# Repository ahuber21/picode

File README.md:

# picode - All code that is run on the Saufhaengerle Raspberry Pi

* [picode - All code that is run on the Saufhaengerle Raspberry Pi](#picode---all-code-that-is-run-on-the-saufhaengerle-raspberry-pi)
  * [Links](#links)
  * [TODO](#todo)
  * [Contents](#contents)
    * [switcher](#switcher)
    * [zapfhahn](#zapfhahn)
  * [Timezone notes](#timezone-notes)
  * [Install pyfingerprint](#install-pyfingerprint)
    * [pyfingerprint - required modifications / hacks](#pyfingerprint---required-modifications--hacks)
  * [Fixing the image download from charBuffer](#fixing-the-image-download-from-charbuffer)
    * [Using fingerprint sensor](#using-fingerprint-sensor)
  * [Valve notes](#valve-notes)
  * [MariaDB notes](#mariadb-notes)
    * [phpMyAdmin](#phpmyadmin)
    * [Grafana](#grafana)

## Links

* saufanlage myPhpAdmin: http://saufanlage.local:81/http://saufanlage.local:81/phpmyadmin/
  * suffi - NU-AD-76
* saufanlage grafana: http://saufanlage.local:3000
  * admin - NU-AD-76

## TODO

* Multiple fingers per user
  * Fingerprint class?
* Only valves that are registered for user
* Auto-close when idle, i.e. no quantity for x seconds
* Logs to website
* Web terminal
* Android app with push notifications
  * some statistics for every tap
* Web interface for valve/daemon configuration
* Web interface to start calib?
* Warning when tapped quantity threshold is reached
* 4 digit display

Code here is set up for python version 3.X and all required packages are defined in `requirements.txt`.

To set up the RPi do

```bash
# first make sure you installed python3.X + some dev libs
sudo apt-get install python3 python3-dev libtiff5-dev zlib1g-dev libfreetype6-dev liblcms2-dev libwebp-dev libharfbuzz-dev libfribidi-dev tcl8.6-dev tk8.6-dev python-tk git python3-venv emacs devscripts equivs libjpeg-dev apt-get install python3-dev
```

(most of the requirements are for `Pillow` which is required by pyfingerprint)

Now set up the virtual environment

```bash
git clone --recursive https://gitlab.com/saufhaengerle/picode
cd picode
python3.7 -m venv venv
source venv/bin/activate
pip install -r requirements.txt
```

If you want to set up the repository for development, **additional steps** are required. After completing the steps above do

```bash
pre-commit install
```

## Contents

### switcher

A webapp that can switch attached relays. Usually used for switching lights.

Notes:

* Bootstrap version 2.3.2
* Bootstrap toggle from http://www.bootstraptoggle.com/

### zapfhahn

All the code that is required to run the Zapfhahn.

## Timezone notes

Make sure that you select the correct timezone!

```bash
$ sudo raspi-config
# select Europe/Berlin in option '4. Localisation options'
```

## Install pyfingerprint

```bash
# dirty hack because pip install does not actually install the package, only sets the context
mkdir venv/lib/python3.5/site-packages/pyfingerprint
cp src/zapfhahn/hardware/pyfingerprint/src/files/pyfingerprint/pyfingerprint.py venv/lib/python3.5/site-packages/pyfingerprint
```

In order to use the Raspberry Pi's serial port I had to make change that is explained [here](https://raspberrypi.stackexchange.com/questions/45570/how-do-i-make-serial-work-on-the-raspberry-pi3-pi3b-pizerow/45571#45571). More informatio$

Do

```bash
sudo emacs -nw /boot/config.txt
```

and add the lines

```
enable_uart=1
dtoverlay=pi3-disable-bt
```

Further /boot/cmdline.txt needs some editing to prevent the console from using the UART

```bash
sudo emacs -nw /boot/cmdline.txt
```

and remove the following entry

```
console=serial0,115200
```

It is also necessary to disable the system service that initialises the modem so it doesn't use the UART: `sudo systemctl disable hciuart`.

After rebooting, this will make the uart pins available as `/dev/ttyAMA0` or better `/dev/serial0`.

To install minicom use

```bash
$ sudo apt-get install minicom
```

Now you can test the serial port, shortcut TX and RX on the pi and run the following code

```bash
$ sudo minicom -b 57600 -o -D /dev/serial0
```

If everything is working correctly the terminal will echo every keystroke.

### pyfingerprint - required modifications / hacks

We've tried many libraries and the different notes a bit spread over multiple READMEs.
Now we are using the pyfingerprint library directly in python and the notes about the wiring are in the [FPM-pi README](https://gitlab.com/saufhaengerle/picode/blob/master/src/zapfhahn/hardware/FPM-pi/README.md)

There is a special feature about the R551 sensor that needs a slight modification in the pyfingerprint library.
It is discussed in [this thread](https://github.com/brianrho/FPM/issues/8) and the fix for python is inspired by [these lines](if (page == 0 && group_idx == 0 && fid == 0)).

The point is that when scanning the page IDs for some reason the first bit in the first pageElement is always `False`.
This makes the library think that ID#0 is free, always.
For that reason the first entry must be skipped.
Specifically, this means replacing these lines

```python
# in pyfingerprint.py - function is getTemplateIndex(self, page)
for pageElement in pageElements:
    ## Test every bit (bit = template position is used indicator) of a table page element
    for p in range(0, 7 + 1):
        positionIsUsed = (self.__bitAtPosition(pageElement, p) == 1)
        templateIndex.append(positionIsUsed)
```

with

```python
for idx, pageElement in enumerate(pageElements):
    ## Test every bit (bit = template position is used indicator) of a table page element
    for p in range(0, 7 + 1):
        if idx == 0 and p == 0: continue
        positionIsUsed = (self.__bitAtPosition(pageElement, p) == 1)
        templateIndex.append(positionIsUsed)
```

## Fixing the image download from charBuffer

In the `loadTemplate` method something goes wrong.
We have to replace

```python
        packetPayload = (
            FINGERPRINT_LOADTEMPLATE,
            charBufferNumber,
            self.__rightShift(positionNumber, 8),
            self.__rightShift(positionNumber, 0),
        )
```

with

```python
        packetPayload = (
            FINGERPRINT_LOADTEMPLATE,
            charBufferNumber,
            self.__rightShift(positionNumber, 8),
            self.__rightShift(positionNumber, 0) & 0xFF,
        )
```

i.e., we have to add the `& 0xFF` part.

### Using fingerprint sensor

We use the [WiringPi](http://wiringpi.com/download-and-install/) library to provide the external functions.

**WiringPi is pre-installed on raspian!**

This code was developed using

```bash
pi@octopi:~/saufhaengerle/picode/src/zapfhahn/hardware/FPM-C $ gpio -v
gpio version: 2.46
Copyright (c) 2012-2018 Gordon Henderson
This is free software with ABSOLUTELY NO WARRANTY.
For details type: gpio -warranty

Raspberry Pi Details:
  Type: Pi 3, Revision: 02, Memory: 1024MB, Maker: Sony
  * Device tree is enabled.
  *--> Raspberry Pi 3 Model B Rev 1.2
  * This Raspberry Pi supports user-level GPIO access.
```

In order to use the Raspberry Pi's serial port I had to make change that is explained [here](https://raspberrypi.stackexchange.com/questions/45570/how-do-i-make-serial-work-on-the-raspberry-pi3-pi3b-pizerow/45571#45571). More information can also be found [here](https://www.raspberrypi.org/documentation/configuration/uart.md)

Do

```bash
sudo emacs -nw /boot/config.txt
```

and add the lines

```
enable_uart=1
dtoverlay=pi3-disable-bt
```

Further /boot/cmdline.txt needs some editing to prevent the console from using the UART

```bash
sudo emacs -nw /boot/cmdline.txt
```

and remove the following entry

```
console=serial0,115200
```

It is also necessary to disable the system service that initialises the modem so it doesn't use the UART: `sudo systemctl disable hciuart`.

After rebooting, this will make the uart pins available as `/dev/ttyAMA0` or better `/dev/serial0`.

The code can be compiled using

 ```bash
 gcc -lwiringPi -o test fpm_raspi.c
 ```

 #### Wiring

The picture shows how the sensor was connected to the RPi.

It is installed according to the manual, with pins 1 and 7 left disconnected.
Only the UART, 3.3V and GND pins are connected.

The pins on the RPi 3 Model B are labeled like this

The pins on the Raspberry Pi Zero are labeled like this

We have these connections

| Sensor pin | Sensor cable color | RPi pin       | RPi color     | Comment           |
|------------|--------------------|---------------|---------------|-------------------|
| 1          | orange             | not connected |               |                   |
| 2          | white              | 3.3V/01       | black         |                   |
| 3          | blue               | GPIO15 TX/10  | orange/purple | RPi TX->Sensor RX |
| 4          | green              | GPIO14 RX/08  | yellow/blue   | RPi RX->Sensor TX |
| 5          | yellow             | GND           | green         |                   |
| 6          | black              | 3.3V/17       | yellow        |                   |
| 7          | red                | not connected |               |                   |

## Valve notes

The valves run on 12V DC power.
The polarity does not matter.
We connect them to a relay that controls their state.
In my test setup I connected them to the normally open (NO) port.
That is because the data pin is usually in HIGH mode and we have to explicitly pull it down.
Like this, the current draw is 0 until we open it with `valve.open()`.
The logic side of the 5V relay was connected GND, Vcc = 5V and the data pin was connected to the raspberry pi **using a logic level converter**.

## MariaDB notes

```bash
sudo apt-get install mariadb-server
```

Then run the setup script

```bash
$ sudo mysql_secure_installation

NOTE: RUNNING ALL PARTS OF THIS SCRIPT IS RECOMMENDED FOR ALL MariaDB
      SERVERS IN PRODUCTION USE!  PLEASE READ EACH STEP CAREFULLY!

In order to log into MariaDB to secure it, we'll need the current
password for the root user.  If you've just installed MariaDB, and
you haven't set the root password yet, the password will be blank,
so you should just press enter here.

Enter current password for root (enter for none):
OK, successfully used password, moving on...

Setting the root password ensures that nobody can log into the MariaDB
root user without the proper authorisation.

You already have a root password set, so you can safely answer 'n'.

Change the root password? [Y/n] n
 ... skipping.

By default, a MariaDB installation has an anonymous user, allowing anyone
to log into MariaDB without having to have a user account created for
them.  This is intended only for testing, and to make the installation
go a bit smoother.  You should remove them before moving into a
production environment.

Remove anonymous users? [Y/n] n
 ... skipping.

Normally, root should only be allowed to connect from 'localhost'.  This
ensures that someone cannot guess at the root password from the network.

Disallow root login remotely? [Y/n] Y
 ... Success!

By default, MariaDB comes with a database named 'test' that anyone can
access.  This is also intended only for testing, and should be removed
before moving into a production environment.

Remove test database and access to it? [Y/n] Y
 - Dropping test database...
 ... Success!
 - Removing privileges on test database...
 ... Success!

Reloading the privilege tables will ensure that all changes made so far
will take effect immediately.

Reload privilege tables now? [Y/n] Y
 ... Success!

Cleaning up...

All done!  If you've completed all of the above steps, your MariaDB
installation should now be secure.

Thanks for using MariaDB!
```

Create a user with privileges that is allowed to connect from subnet

```
$ sudo mysql -u root
Welcome to the MariaDB monitor.  Commands end with ; or \g.
Your MariaDB connection id is 9
Server version: 10.1.38-MariaDB-0+deb9u1 Raspbian 9.0

Copyright (c) 2000, 2018, Oracle, MariaDB Corporation Ab and others.

Type 'help;' or '\h' for help. Type '\c' to clear the current input statement.

MariaDB [(none)]> GRANT ALL PRIVILEGES ON *.* TO 'suffi'@'localhost' IDENTIFIED BY 'NU-AD-76';
Query OK, 0 rows affected (0.00 sec)
```

We also add a read-only user for grafana

```bash
GRANT SELECT,SHOW VIEW ON *.* TO 'grafana'@'localhost' IDENTIFIED BY 'grafana_view_user';
```

#### Backing up the DB

Export it using

```bash
$ mysqldump -u suffi -p SaufDatabase > SaufDatabase.sql.bak
```

Import it with

```bash
# only necessary if the DB doesn't already exist
$ mysql -u suffi -p
CREATE DATABASE SaufDatabase;
```

and

```bash
mysql -u suffi -p SaufDatabase < SaufDatabase.sql.bak
```

### phpMyAdmin

```bash
sudo apt-get install phpmyadmin
# note: select apache2 if asked
# select yes when asked if you want to generate a DB
# provide password (recommended NU-AD-76)
```

Add phpmyadmin apache conf

```bash
$ sudo emacs -nw /etc/apache2/apache2.conf
# at bottom insert
Include /etc/phpmyadmin/apache.conf
# restart apache
$ sudo /etc/init.d/apache2 restart
```

If you want to make the server listen to a different port edit

```bash
$ sudo emacs -nw /etc/apache2/apache2.conf
$ sudo /etc/init.d/apache2 restart
```

Link the phpMyAdmin landing page

```bash
sudo ln -s /usr/share/phpmyadmin /var/www/html
```

Now you can connect to it, e.g. on `http://192.168.178.86:81/phpmyadmin`

### Grafana

```bash
$ wget https://dl.grafana.com/oss/release/grafana-rpi_6.2.1_armhf.deb
$ sudo dpkg -i grafana-rpi_6.2.1_armhf.deb
```

Add grafana to autostart

```bash
$ sudo /bin/systemctl daemon-reload
$ sudo /bin/systemctl enable grafana-server
```

The grafana server is listening on port 3000.
Log in on `http://192.168.178.86:3000` using user admin with password admin.
Grafana will ask you to change the PW after your first login.
Of course we change it to NU-AD-76.

There we can add a database

* Type: MySQL
* Host: localhost:3306
* Database: SaufDatabase
* User: grafana
* Password: grafana_view_user

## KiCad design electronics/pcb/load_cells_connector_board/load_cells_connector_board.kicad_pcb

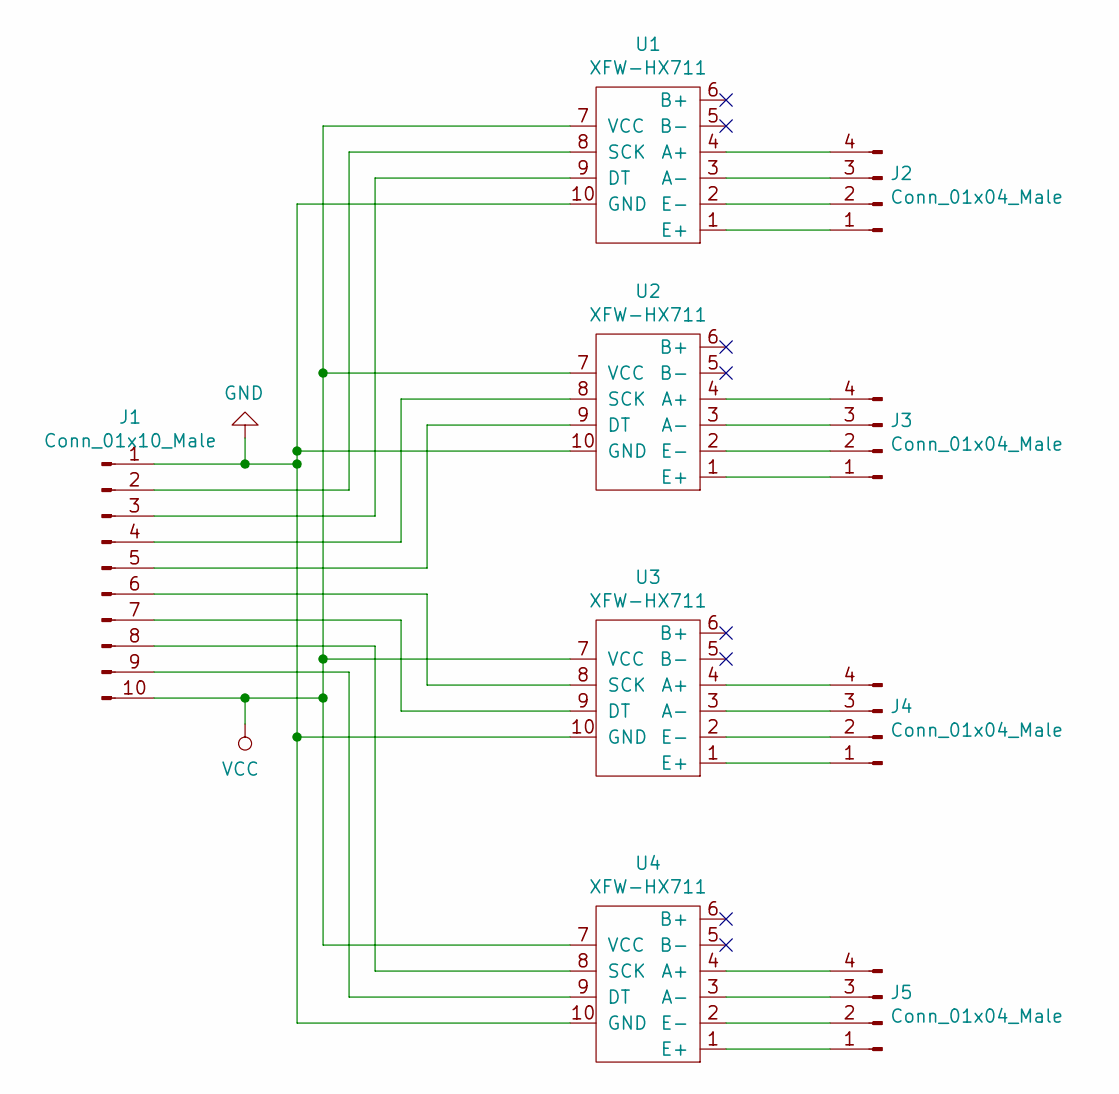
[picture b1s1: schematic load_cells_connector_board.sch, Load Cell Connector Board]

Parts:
J1: Conn_01x10_Male; Molex_KK-254_AE-6410-10A_1x10_P2.54mm_Vertical
J2, J3, J4, J5: Conn_01x04_Male; Molex_KK-254_AE-6410-04A_1x04_P2.54mm_Vertical
U1, U2, U3, U4: XFW-HX711

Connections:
GND: J1.1, U1.10 (GND), U2.10 (GND), U3.10 (GND), U4.10 (GND)
unnamed: J1.2, U1.8 (SCK)
unnamed: J1.3, U1.9 (DT)
unnamed: J1.4, U2.8 (SCK)
unnamed: J1.5, U2.9 (DT)
unnamed: J1.6, U3.8 (SCK)
unnamed: J1.7, U3.9 (DT)
unnamed: J1.8, U4.8 (SCK)
unnamed: J1.9, U4.9 (DT)
unnamed: J2.1, U1.1 (E+)
unnamed: J2.2, U1.2 (E-)
unnamed: J2.3, U1.3 (A-)
unnamed: J2.4, U1.4 (A+)
unnamed: J3.1, U2.1 (E+)
unnamed: J3.2, U2.2 (E-)
unnamed: J3.3, U2.3 (A-)
unnamed: J3.4, U2.4 (A+)
unnamed: J4.1, U3.1 (E+)
unnamed: J4.2, U3.2 (E-)
unnamed: J4.3, U3.3 (A-)
unnamed: J4.4, U3.4 (A+)
unnamed: J5.1, U4.1 (E+)
unnamed: J5.2, U4.2 (E-)
unnamed: J5.3, U4.3 (A-)
unnamed: J5.4, U4.4 (A+)
VCC: J1.10, U1.7 (VCC), U2.7 (VCC), U3.7 (VCC), U4.7 (VCC)

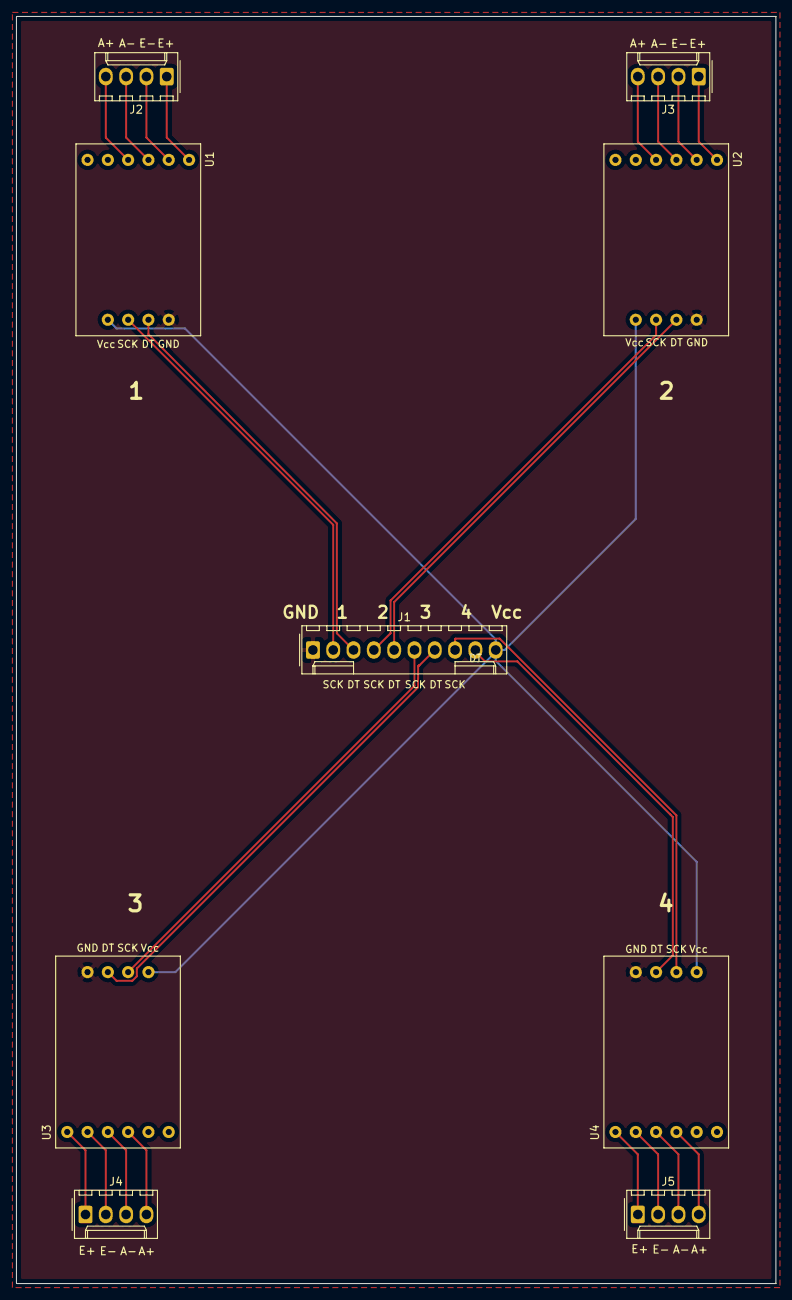
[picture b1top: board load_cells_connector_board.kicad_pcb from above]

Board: 2 copper layers, 95.0 x 158.5 mm, 9 parts (0 on the bottom side), 26 nets.

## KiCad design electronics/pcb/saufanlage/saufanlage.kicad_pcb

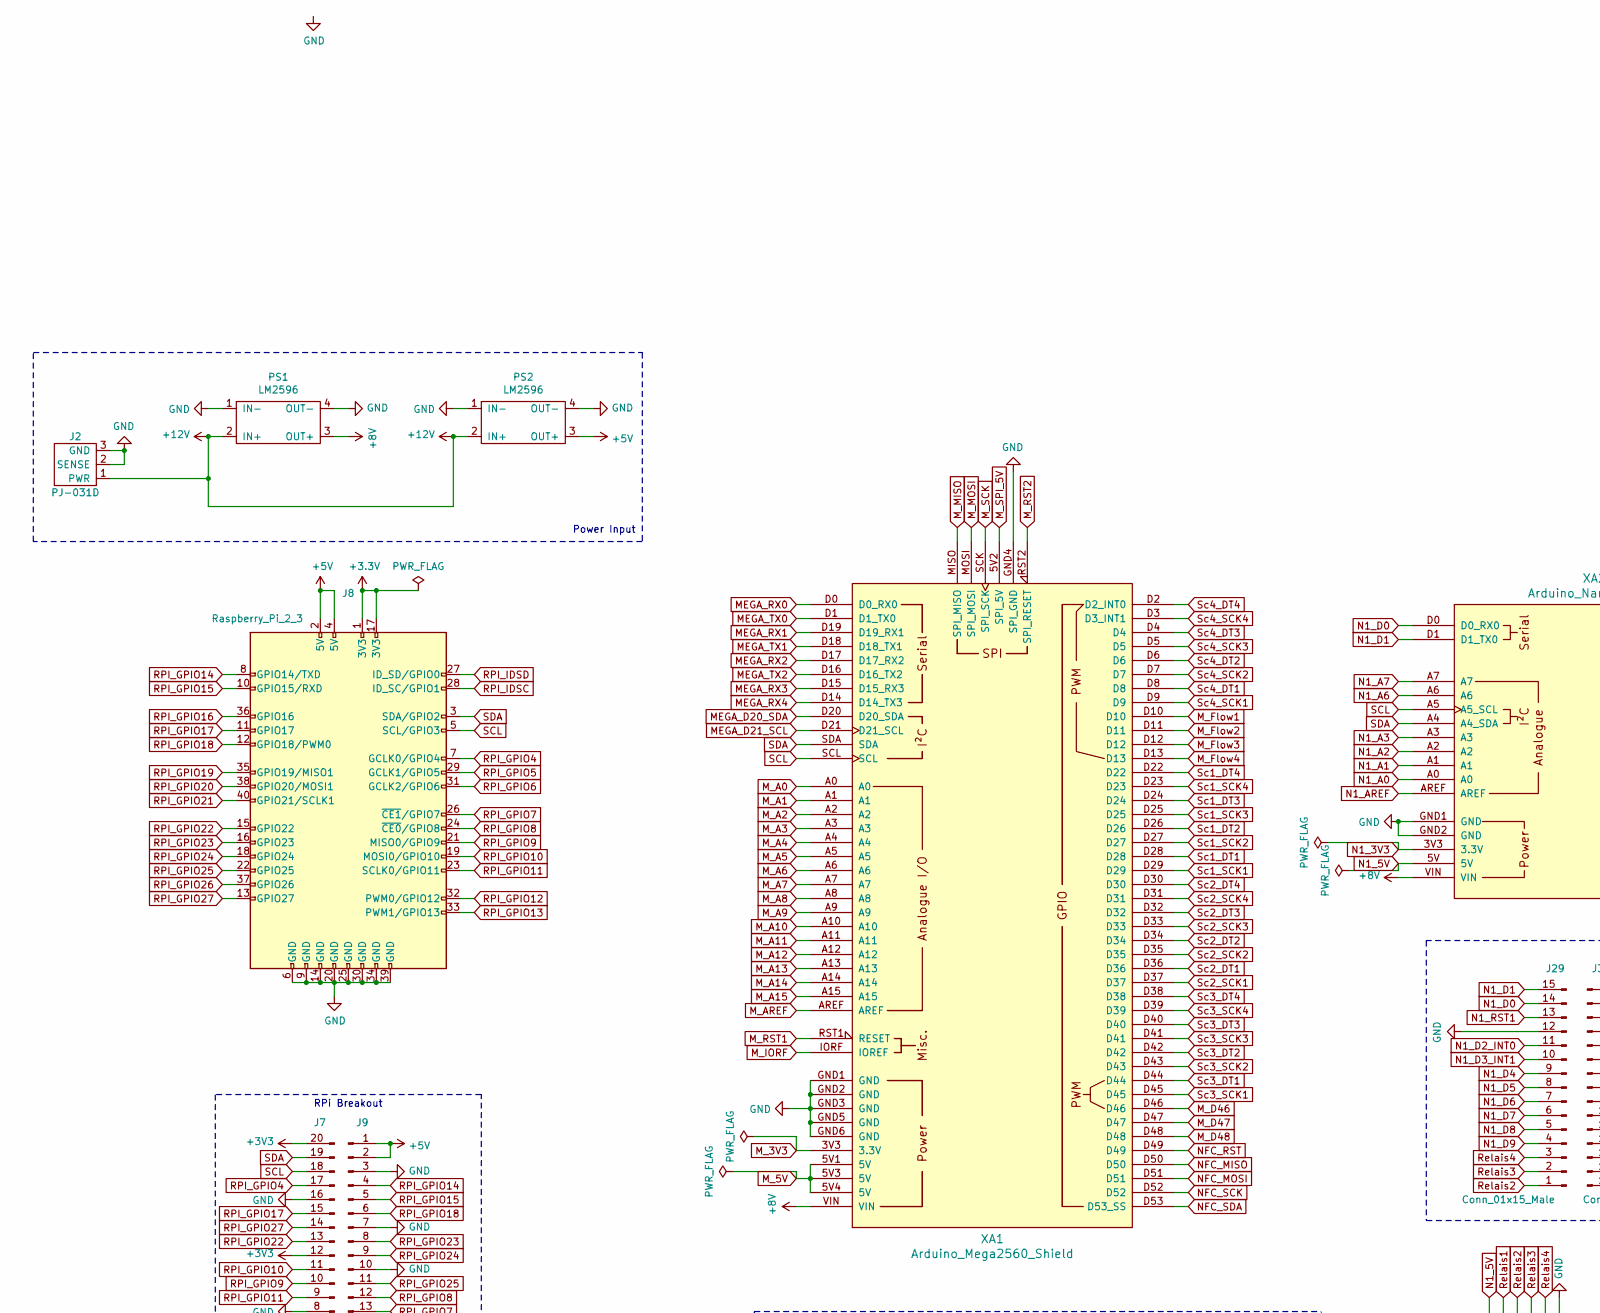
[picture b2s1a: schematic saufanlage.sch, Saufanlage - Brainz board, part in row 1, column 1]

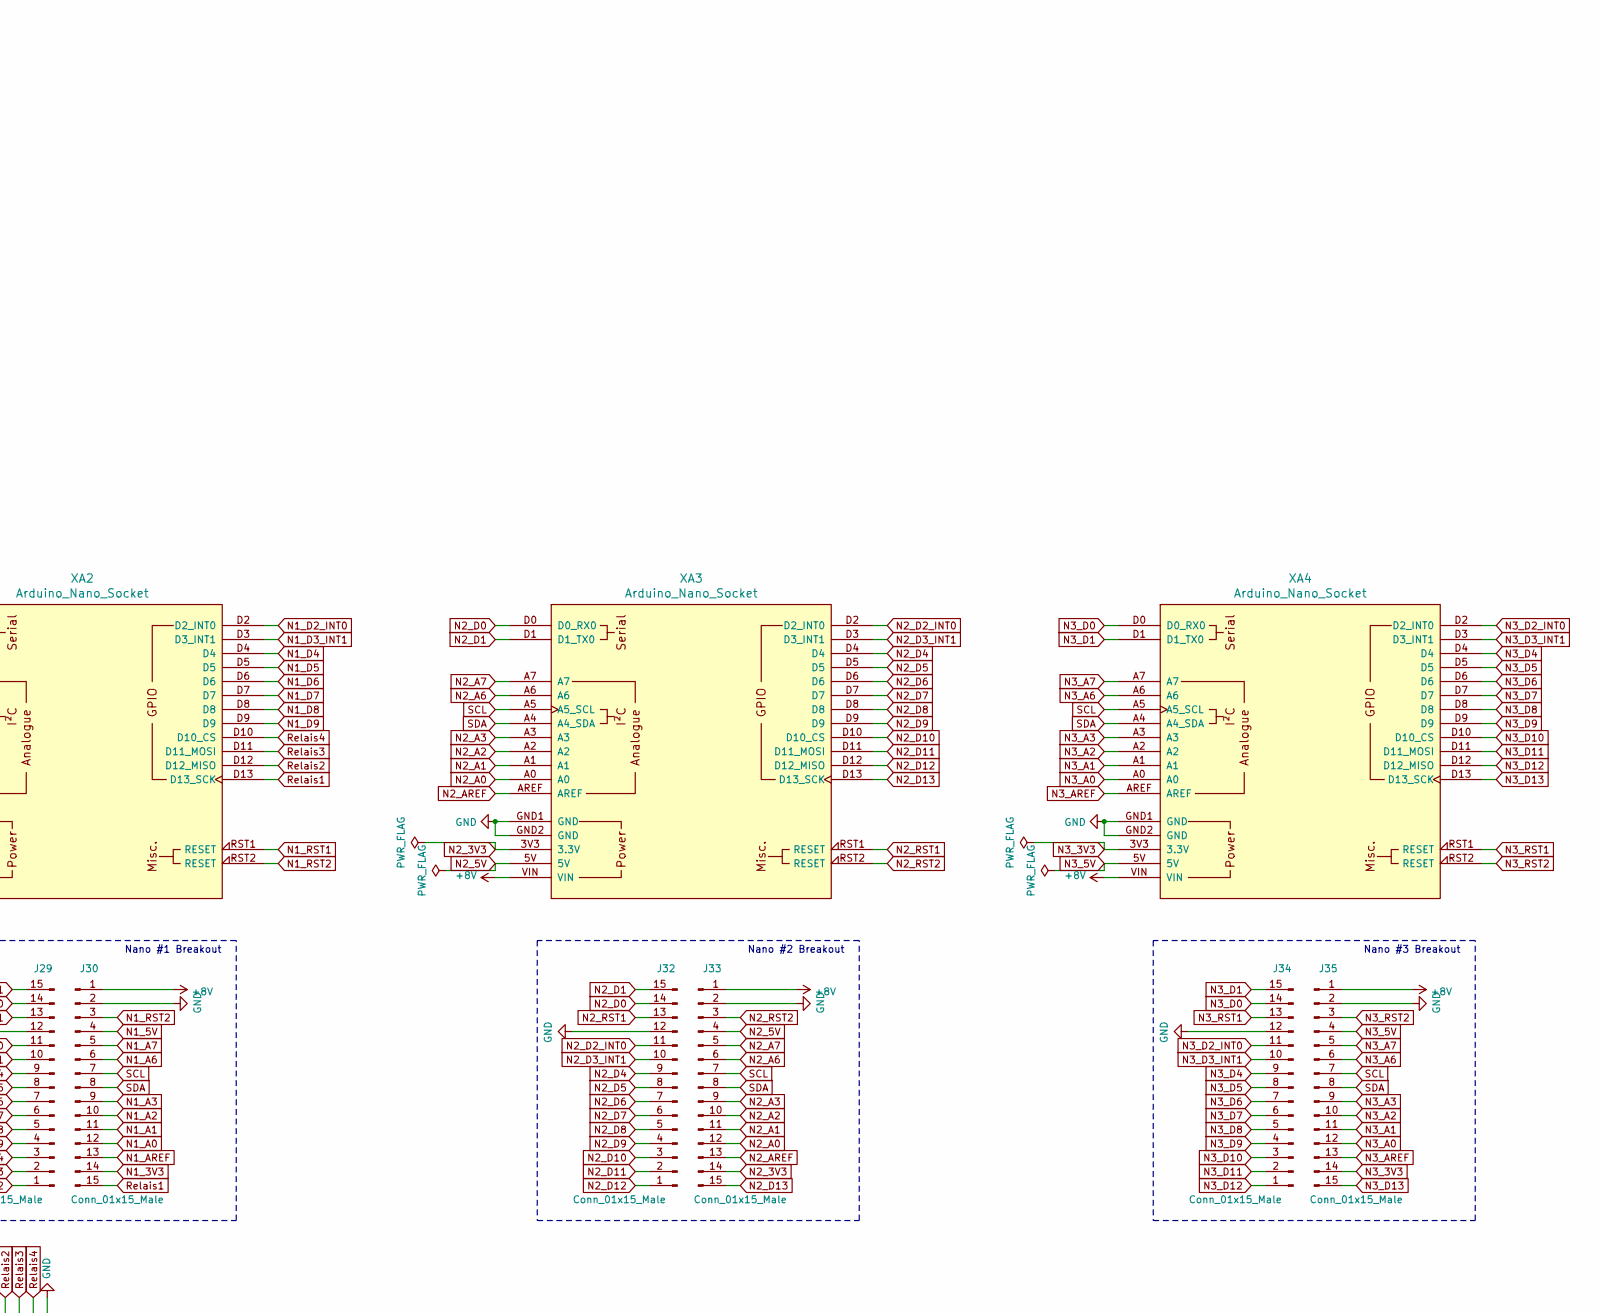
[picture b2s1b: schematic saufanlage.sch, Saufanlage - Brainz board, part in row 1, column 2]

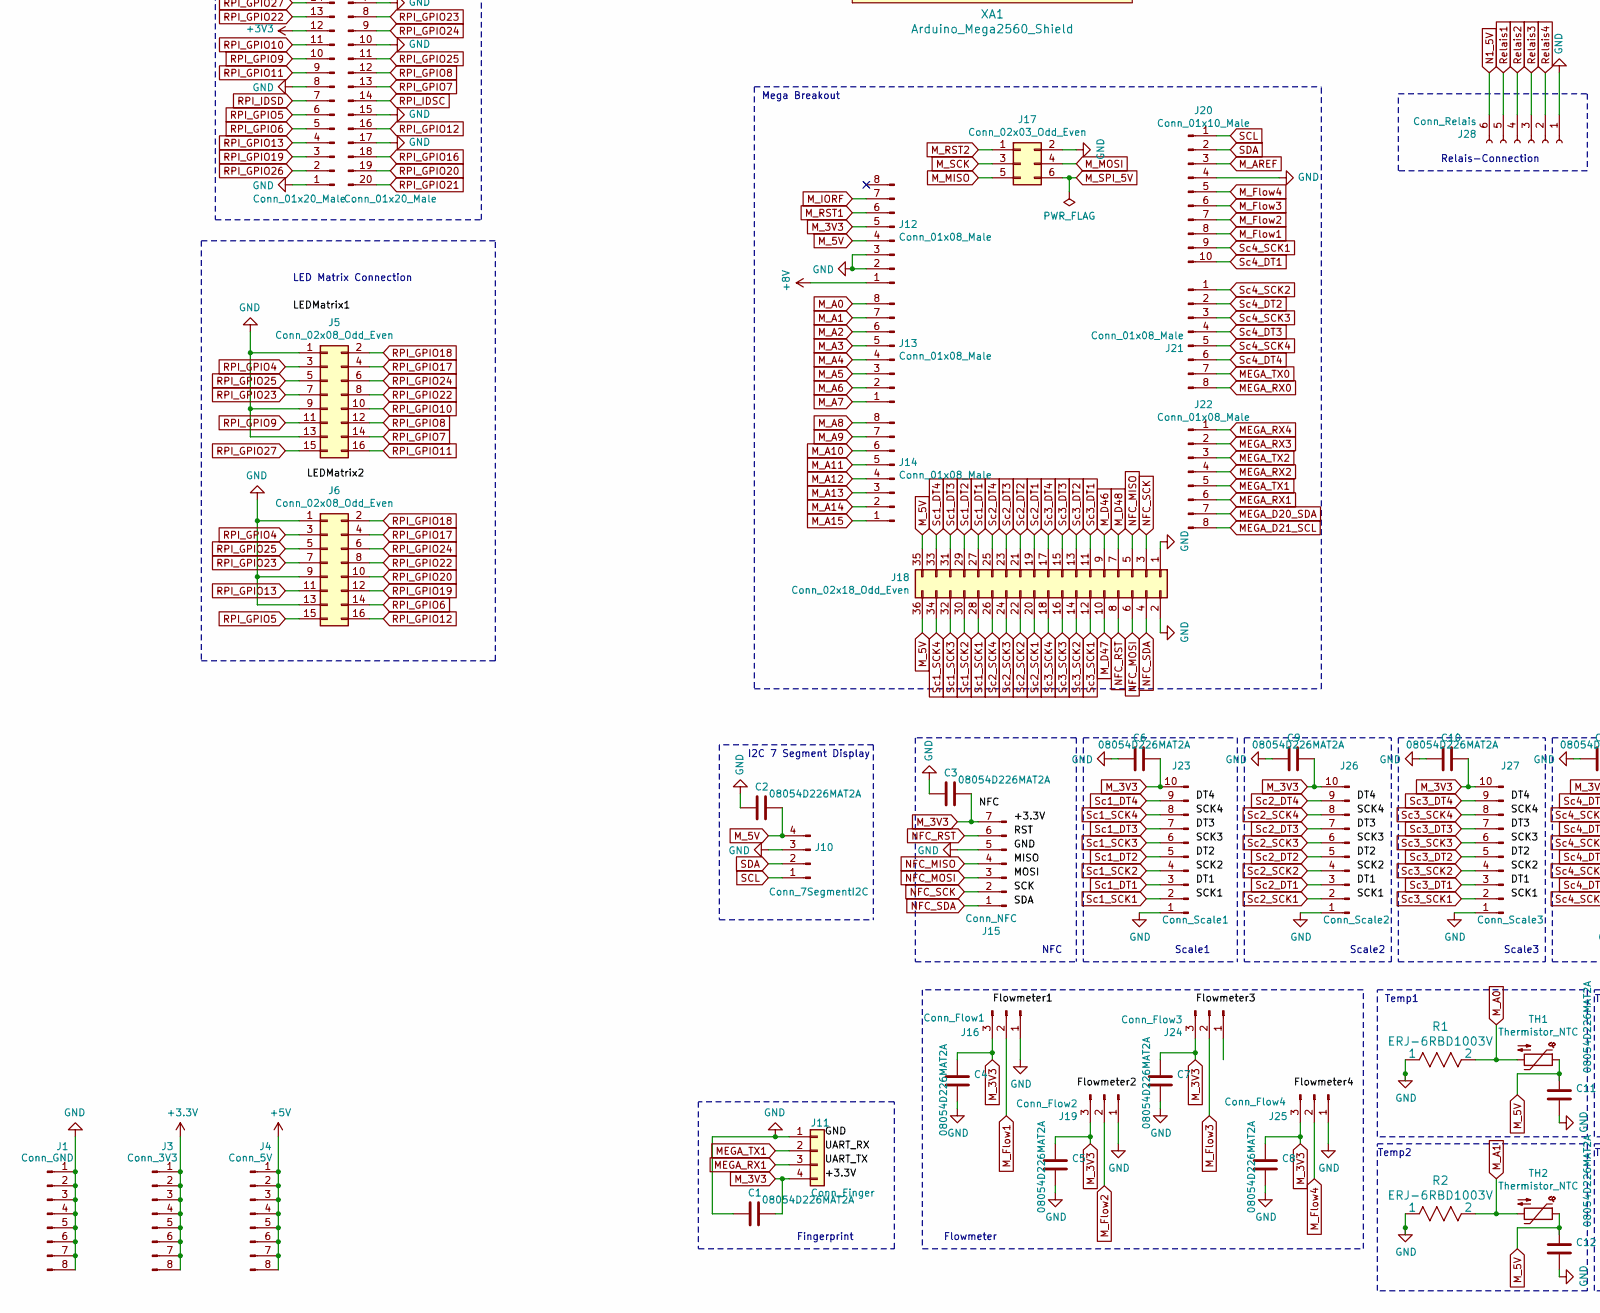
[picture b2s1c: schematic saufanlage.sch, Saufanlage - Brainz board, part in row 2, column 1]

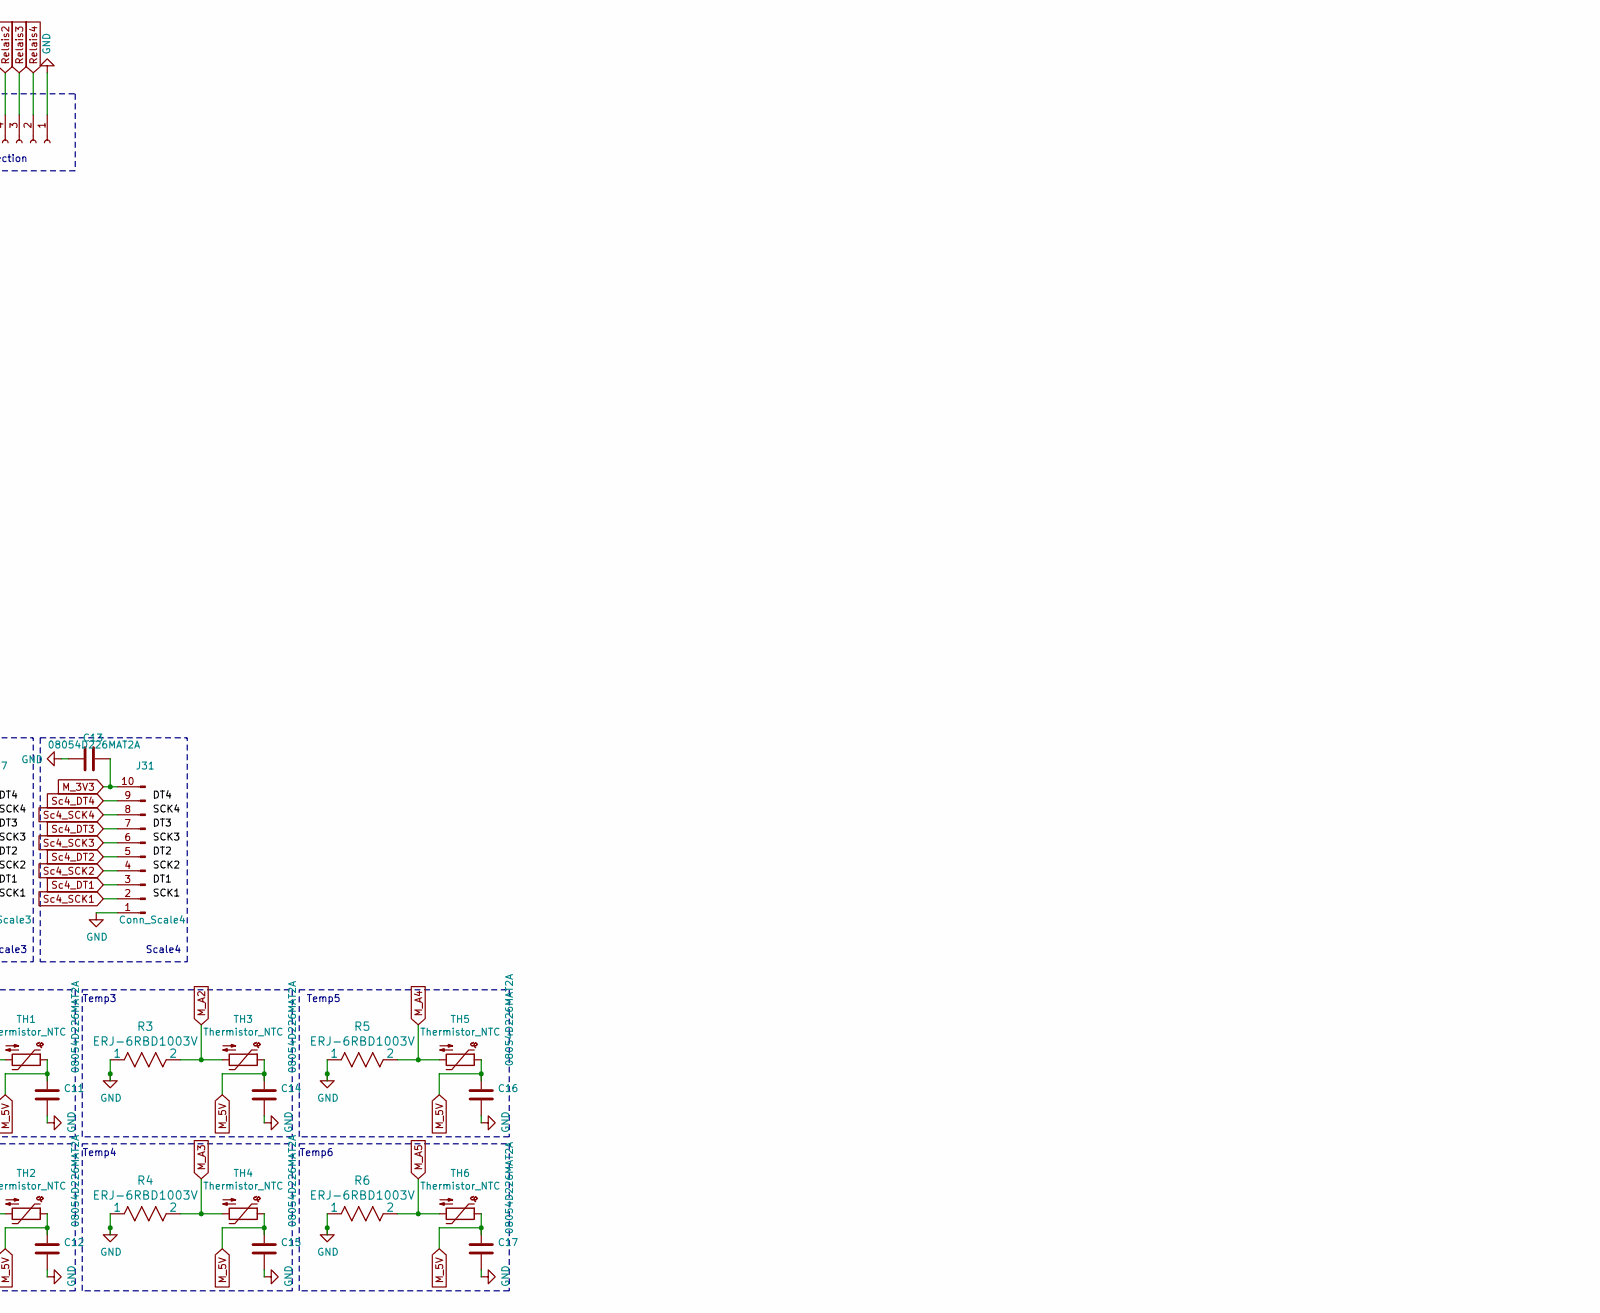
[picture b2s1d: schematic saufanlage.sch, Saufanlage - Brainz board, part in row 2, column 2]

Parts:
C1, C2, C3, C4, C5, C6, C7, C8, C9, C10, C11, C12, C13, C14, C15, C16, C17: 08054D226MAT2A; C_0805_2012Metric_Pad1.15x1.40mm_HandSolder
J1: Conn_GND; PinHeader_1x08_P2.54mm_Vertical
J2: PJ-031D; CUI_PJ-031D
J3: Conn_3V3; PinHeader_1x08_P2.54mm_Vertical
J4: Conn_5V; PinHeader_1x08_P2.54mm_Vertical
J5, J6: Conn_02x08_Odd_Even; PinHeader_2x08_P2.54mm_Vertical
J7, J9: Conn_01x20_Male; PinHeader_1x20_P2.54mm_Vertical
J8: Raspberry_Pi_2_3; PinHeader_2x20_P2.54mm_Vertical
J10: Conn_7SegmentI2C; PinHeader_1x04_P2.54mm_Vertical
J11: Conn_Finger; PinHeader_1x04_P2.54mm_Vertical
J12, J13, J14, J21, J22: Conn_01x08_Male; PinHeader_1x08_P2.54mm_Vertical
J15: Conn_NFC; PinHeader_1x07_P2.54mm_Vertical
J16: Conn_Flow1; PinHeader_1x03_P2.54mm_Vertical
J17: Conn_02x03_Odd_Even; PinHeader_2x03_P2.54mm_Vertical
J18: Conn_02x18_Odd_Even; PinHeader_2x18_P2.54mm_Vertical
J19: Conn_Flow2; PinHeader_1x03_P2.54mm_Vertical
J20: Conn_01x10_Male; PinHeader_1x10_P2.54mm_Vertical
J23: Conn_Scale1; PinHeader_1x10_P2.54mm_Vertical
J24: Conn_Flow3; PinHeader_1x03_P2.54mm_Vertical
J25: Conn_Flow4; PinHeader_1x03_P2.54mm_Vertical
J26: Conn_Scale2; PinHeader_1x10_P2.54mm_Vertical
J27: Conn_Scale3; PinHeader_1x10_P2.54mm_Vertical
J28: Conn_Relais; PinHeader_1x06_P2.54mm_Vertical
J29, J30, J32, J33, J34, J35: Conn_01x15_Male; PinHeader_1x15_P2.54mm_Vertical
J31: Conn_Scale4; PinHeader_1x10_P2.54mm_Vertical
PS1, PS2: LM2596
R1, R2, R3, R4, R5, R6: ERJ-6RBD1003V; R_0805_2012Metric_Pad1.15x1.40mm_HandSolder
TH1, TH2, TH3, TH4, TH5, TH6: Thermistor_NTC; PinHeader_1x02_P2.54mm_Vertical
XA1: Arduino_Mega2560_Shield
XA2, XA3, XA4: Arduino_Nano_Socket

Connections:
+5V: J4.1, J4.2, J4.3, J4.4, J4.5, J4.6, J4.7, J4.8, J8.2 (5V), J8.4 (5V), J9.1, J9.2, PS2.3 (OUT+)
+8V: J12.1, J30.1, J33.1, J35.1, PS1.3 (OUT+), XA1.VIN, XA2.VIN, XA3.VIN, XA4.VIN
+12V: J2.1 (PWR), PS1.2 (IN+), PS2.2 (IN+)
GND: C1.1, C2.1, C3.1, C4.1, C5.1, C6.1, C7.1, C8.1, C9.1, C10.1, C11.1, C12.1, C13.1, C14.1, C15.1, C16.1, C17.1, J1.1, J1.2, J1.3, J1.4, J1.5, J1.6, J1.7, J1.8, J2.2 (SENSE), J2.3 (GND), J5.1, J5.9, J5.13, J6.1, J6.9, J6.13, J7.1, J7.8, J7.16, J8.6 (GND), J8.9 (GND), J8.14 (GND), J8.20 (GND), J8.25 (GND), J8.30 (GND), J8.34 (GND), J8.39 (GND), J9.3, J9.7, J9.10, J9.15, J9.17, J10.3, J11.1, J12.2, J12.3, J15.5, J16.1, J17.2, J18.1, J18.2, J19.1, J20.4, J23.1, J24.1, J25.1, J26.1, J27.1, J28.1, J29.12, J30.2, J31.1, J32.12, J33.2, J34.12, J35.2, PS1.1 (IN-), PS1.4 (OUT-), PS2.1 (IN-), PS2.4 (OUT-), R1.1, R2.1, R3.1, R4.1, R5.1, R6.1, XA1.GND1 (GND), XA1.GND2 (GND), XA1.GND3 (GND), XA1.GND4 (SPI_GND), XA1.GND5 (GND), XA1.GND6 (GND), XA2.GND1 (GND), XA2.GND2 (GND), XA3.GND1 (GND), XA3.GND2 (GND), XA4.GND1 (GND), XA4.GND2 (GND)
MEGA_D20_SDA: J22.7, XA1.D20 (D20_SDA)
MEGA_D21_SCL: J22.8, XA1.D21 (D21_SCL)
MEGA_RX0: J21.8, XA1.D0 (D0_RX0)
MEGA_RX1: J11.3, J22.6, XA1.D19 (D19_RX1)
MEGA_RX2: J22.4, XA1.D17 (D17_RX2)
MEGA_RX3: J22.2, XA1.D15 (D15_RX3)
MEGA_RX4: J22.1, XA1.D14 (D14_TX3)
MEGA_TX0: J21.7, XA1.D1 (D1_TX0)
MEGA_TX1: J11.2, J22.5, XA1.D18 (D18_TX1)
MEGA_TX2: J22.3, XA1.D16 (D16_TX2)
M_3V3: C1.2, C3.2, C4.2, C5.2, C6.2, C7.2, C8.2, C9.2, C10.2, C13.2, J11.4, J12.5, J15.7, J16.3, J19.3, J23.10, J24.3, J25.3, J26.10, J27.10, J31.10, XA1.3V3 (3.3V)
M_5V: C2.2, C11.2, C12.2, C14.2, C15.2, C16.2, C17.2, J10.4, J12.4, J18.35, J18.36, TH1.1, TH2.1, TH3.1, TH4.1, TH5.1, TH6.1, XA1.5V1 (5V), XA1.5V3 (5V), XA1.5V4 (5V)
M_A0: J13.8, R1.2, TH1.2, XA1.A0
M_A1: J13.7, R2.2, TH2.2, XA1.A1
M_A2: J13.6, R3.2, TH3.2, XA1.A2
M_A3: J13.5, R4.2, TH4.2, XA1.A3
M_A4: J13.4, R5.2, TH5.2, XA1.A4
M_A5: J13.3, R6.2, TH6.2, XA1.A5
M_A6: J13.2, XA1.A6
M_A7: J13.1, XA1.A7
M_A8: J14.8, XA1.A8
M_A9: J14.7, XA1.A9
M_A10: J14.6, XA1.A10
M_A11: J14.5, XA1.A11
M_A12: J14.4, XA1.A12
M_A13: J14.3, XA1.A13
M_A14: J14.2, XA1.A14
M_A15: J14.1, XA1.A15
M_AREF: J20.3, XA1.AREF
M_D46: J18.9, XA1.D46
M_D47: J18.10, XA1.D47
M_D48: J18.7, XA1.D48
M_Flow1: J16.2, J20.8, XA1.D10
M_Flow2: J19.2, J20.7, XA1.D11
M_Flow3: J20.6, J24.2, XA1.D12
M_Flow4: J20.5, J25.2, XA1.D13
M_IORF: J12.7, XA1.IORF (IOREF)
M_MISO: J17.5, XA1.MISO (SPI_MISO)
M_MOSI: J17.4, XA1.MOSI (SPI_MOSI)
M_RST1: J12.6, XA1.RST1 (RESET)
M_RST2: J17.1, XA1.RST2 (SPI_RESET)
M_SCK: J17.3, XA1.SCK (SPI_SCK)
M_SPI_5V: J17.6, XA1.5V2 (SPI_5V)
N1_3V3: J30.14, XA2.3V3 (3.3V)
N1_5V: J28.6, J30.4, XA2.5V
N1_A0: J30.12, XA2.A0
N1_A1: J30.11, XA2.A1
N1_A2: J30.10, XA2.A2
N1_A3: J30.9, XA2.A3
N1_A6: J30.6, XA2.A6
N1_A7: J30.5, XA2.A7
N1_AREF: J30.13, XA2.AREF
N1_D0: J29.14, XA2.D0 (D0_RX0)
N1_D1: J29.15, XA2.D1 (D1_TX0)
N1_D2_INT0: J29.11, XA2.D2 (D2_INT0)
N1_D3_INT1: J29.10, XA2.D3 (D3_INT1)
N1_D4: J29.9, XA2.D4
N1_D5: J29.8, XA2.D5
N1_D6: J29.7, XA2.D6
N1_D7: J29.6, XA2.D7
N1_D8: J29.5, XA2.D8
N1_D9: J29.4, XA2.D9
N1_RST1: J29.13, XA2.RST1 (RESET)
N1_RST2: J30.3, XA2.RST2 (RESET)
N2_3V3: J33.14, XA3.3V3 (3.3V)
N2_5V: J33.4, XA3.5V
N2_A0: J33.12, XA3.A0
N2_A1: J33.11, XA3.A1
N2_A2: J33.10, XA3.A2
N2_A3: J33.9, XA3.A3
N2_A6: J33.6, XA3.A6
N2_A7: J33.5, XA3.A7
N2_AREF: J33.13, XA3.AREF
N2_D0: J32.14, XA3.D0 (D0_RX0)
N2_D1: J32.15, XA3.D1 (D1_TX0)
N2_D2_INT0: J32.11, XA3.D2 (D2_INT0)
N2_D3_INT1: J32.10, XA3.D3 (D3_INT1)
N2_D4: J32.9, XA3.D4
N2_D5: J32.8, XA3.D5
N2_D6: J32.7, XA3.D6
N2_D7: J32.6, XA3.D7
N2_D8: J32.5, XA3.D8
N2_D9: J32.4, XA3.D9
N2_D10: J32.3, XA3.D10 (D10_CS)
N2_D11: J32.2, XA3.D11 (D11_MOSI)
N2_D12: J32.1, XA3.D12 (D12_MISO)
N2_D13: J33.15, XA3.D13 (D13_SCK)
N2_RST1: J32.13, XA3.RST1 (RESET)
N2_RST2: J33.3, XA3.RST2 (RESET)
N3_3V3: J35.14, XA4.3V3 (3.3V)
N3_5V: J35.4, XA4.5V
N3_A0: J35.12, XA4.A0
N3_A1: J35.11, XA4.A1
N3_A2: J35.10, XA4.A2
N3_A3: J35.9, XA4.A3
N3_A6: J35.6, XA4.A6
N3_A7: J35.5, XA4.A7
N3_AREF: J35.13, XA4.AREF
N3_D0: J34.14, XA4.D0 (D0_RX0)
N3_D1: J34.15, XA4.D1 (D1_TX0)
N3_D2_INT0: J34.11, XA4.D2 (D2_INT0)
N3_D3_INT1: J34.10, XA4.D3 (D3_INT1)
N3_D4: J34.9, XA4.D4
N3_D5: J34.8, XA4.D5
N3_D6: J34.7, XA4.D6
N3_D7: J34.6, XA4.D7
N3_D8: J34.5, XA4.D8
N3_D9: J34.4, XA4.D9
N3_D10: J34.3, XA4.D10 (D10_CS)
N3_D11: J34.2, XA4.D11 (D11_MOSI)
N3_D12: J34.1, XA4.D12 (D12_MISO)
N3_D13: J35.15, XA4.D13 (D13_SCK)
N3_RST1: J34.13, XA4.RST1 (RESET)
N3_RST2: J35.3, XA4.RST2 (RESET)
NFC_MISO: J15.4, J18.5, XA1.D50
NFC_MOSI: J15.3, J18.6, XA1.D51
NFC_RST: J15.6, J18.8, XA1.D49
NFC_SCK: J15.2, J18.3, XA1.D52
NFC_SDA: J15.1, J18.4, XA1.D53 (D53_SS)
RPI_GPIO4: J5.3, J6.3, J7.17, J8.7 (GCLK0/GPIO4)
RPI_GPIO5: J6.15, J7.6, J8.29 (GCLK1/GPIO5)
RPI_GPIO6: J6.14, J7.5, J8.31 (GCLK2/GPIO6)
RPI_GPIO7: J5.14, J8.26 (~CE1~/GPIO7), J9.13
RPI_GPIO8: J5.12, J8.24 (~CE0~/GPIO8), J9.12
RPI_GPIO9: J5.11, J7.10, J8.21 (MISO0/GPIO9)
RPI_GPIO10: J5.10, J7.11, J8.19 (MOSI0/GPIO10)
RPI_GPIO11: J5.16, J7.9, J8.23 (SCLK0/GPIO11)
RPI_GPIO12: J6.16, J8.32 (PWM0/GPIO12), J9.16
RPI_GPIO13: J6.11, J7.4, J8.33 (PWM1/GPIO13)
RPI_GPIO14: J8.8 (GPIO14/TXD), J9.4
RPI_GPIO15: J8.10 (GPIO15/RXD), J9.5
RPI_GPIO16: J8.36 (GPIO16), J9.18
RPI_GPIO17: J5.4, J6.4, J7.15, J8.11 (GPIO17)
RPI_GPIO18: J5.2, J6.2, J8.12 (GPIO18/PWM0), J9.6
RPI_GPIO19: J6.12, J7.3, J8.35 (GPIO19/MISO1)
RPI_GPIO20: J6.10, J8.38 (GPIO20/MOSI1), J9.19
RPI_GPIO21: J8.40 (GPIO21/SCLK1), J9.20
RPI_GPIO22: J5.8, J6.8, J7.13, J8.15 (GPIO22)
RPI_GPIO23: J5.7, J6.7, J8.16 (GPIO23), J9.8
RPI_GPIO24: J5.6, J6.6, J8.18 (GPIO24), J9.9
RPI_GPIO25: J5.5, J6.5, J8.22 (GPIO25), J9.11
RPI_GPIO26: J7.2, J8.37 (GPIO26)
RPI_GPIO27: J5.15, J7.14, J8.13 (GPIO27)
RPI_IDSC: J8.28 (ID_SC/GPIO1), J9.14
RPI_IDSD: J7.7, J8.27 (ID_SD/GPIO0)
Relais1: J28.5, J30.15, XA2.D13 (D13_SCK)
Relais2: J28.4, J29.1, XA2.D12 (D12_MISO)
Relais3: J28.3, J29.2, XA2.D11 (D11_MOSI)
Relais4: J28.2, J29.3, XA2.D10 (D10_CS)
SCL: J7.18, J8.5 (SCL/GPIO3), J10.1, J20.1, J30.7, J33.7, J35.7, XA1.SCL, XA2.A5 (A5_SCL), XA3.A5 (A5_SCL), XA4.A5 (A5_SCL)
SDA: J7.19, J8.3 (SDA/GPIO2), J10.2, J20.2, J30.8, J33.8, J35.8, XA1.SDA, XA2.A4 (A4_SDA), XA3.A4 (A4_SDA), XA4.A4 (A4_SDA)
Sc1_DT1: J18.27, J23.3, XA1.D28
Sc1_DT2: J18.29, J23.5, XA1.D26
Sc1_DT3: J18.31, J23.7, XA1.D24
Sc1_DT4: J18.33, J23.9, XA1.D22
Sc1_SCK1: J18.28, J23.2, XA1.D29
Sc1_SCK2: J18.30, J23.4, XA1.D27
Sc1_SCK3: J18.32, J23.6, XA1.D25
Sc1_SCK4: J18.34, J23.8, XA1.D23
Sc2_DT1: J18.19, J26.3, XA1.D36
Sc2_DT2: J18.21, J26.5, XA1.D34
Sc2_DT3: J18.23, J26.7, XA1.D32
Sc2_DT4: J18.25, J26.9, XA1.D30
Sc2_SCK1: J18.20, J26.2, XA1.D37
Sc2_SCK2: J18.22, J26.4, XA1.D35
Sc2_SCK3: J18.24, J26.6, XA1.D33
Sc2_SCK4: J18.26, J26.8, XA1.D31
Sc3_DT1: J18.11, J27.3, XA1.D44
Sc3_DT2: J18.13, J27.5, XA1.D42
Sc3_DT3: J18.15, J27.7, XA1.D40
Sc3_DT4: J18.17, J27.9, XA1.D38
Sc3_SCK1: J18.12, J27.2, XA1.D45
Sc3_SCK2: J18.14, J27.4, XA1.D43
Sc3_SCK3: J18.16, J27.6, XA1.D41
Sc3_SCK4: J18.18, J27.8, XA1.D39
Sc4_DT1: J20.10, J31.3, XA1.D8
Sc4_DT2: J21.2, J31.5, XA1.D6
Sc4_DT3: J21.4, J31.7, XA1.D4
Sc4_DT4: J21.6, J31.9, XA1.D2 (D2_INT0)
Sc4_SCK1: J20.9, J31.2, XA1.D9
Sc4_SCK2: J21.1, J31.4, XA1.D7
Sc4_SCK3: J21.3, J31.6, XA1.D5
Sc4_SCK4: J21.5, J31.8, XA1.D3 (D3_INT1)

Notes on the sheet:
LED Matrix Connection
Scale1
Scale2
Fingerprint
Flowmeter
RPi Breakout
NFC
Relais-Connection
Mega Breakout
Nano #1 Breakout
Nano #2 Breakout
Nano #3 Breakout
Power Input
I2C 7 Segment Display
Scale3
Scale4
Temp1
Temp2
Temp4
Temp3
Temp5
Temp6

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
